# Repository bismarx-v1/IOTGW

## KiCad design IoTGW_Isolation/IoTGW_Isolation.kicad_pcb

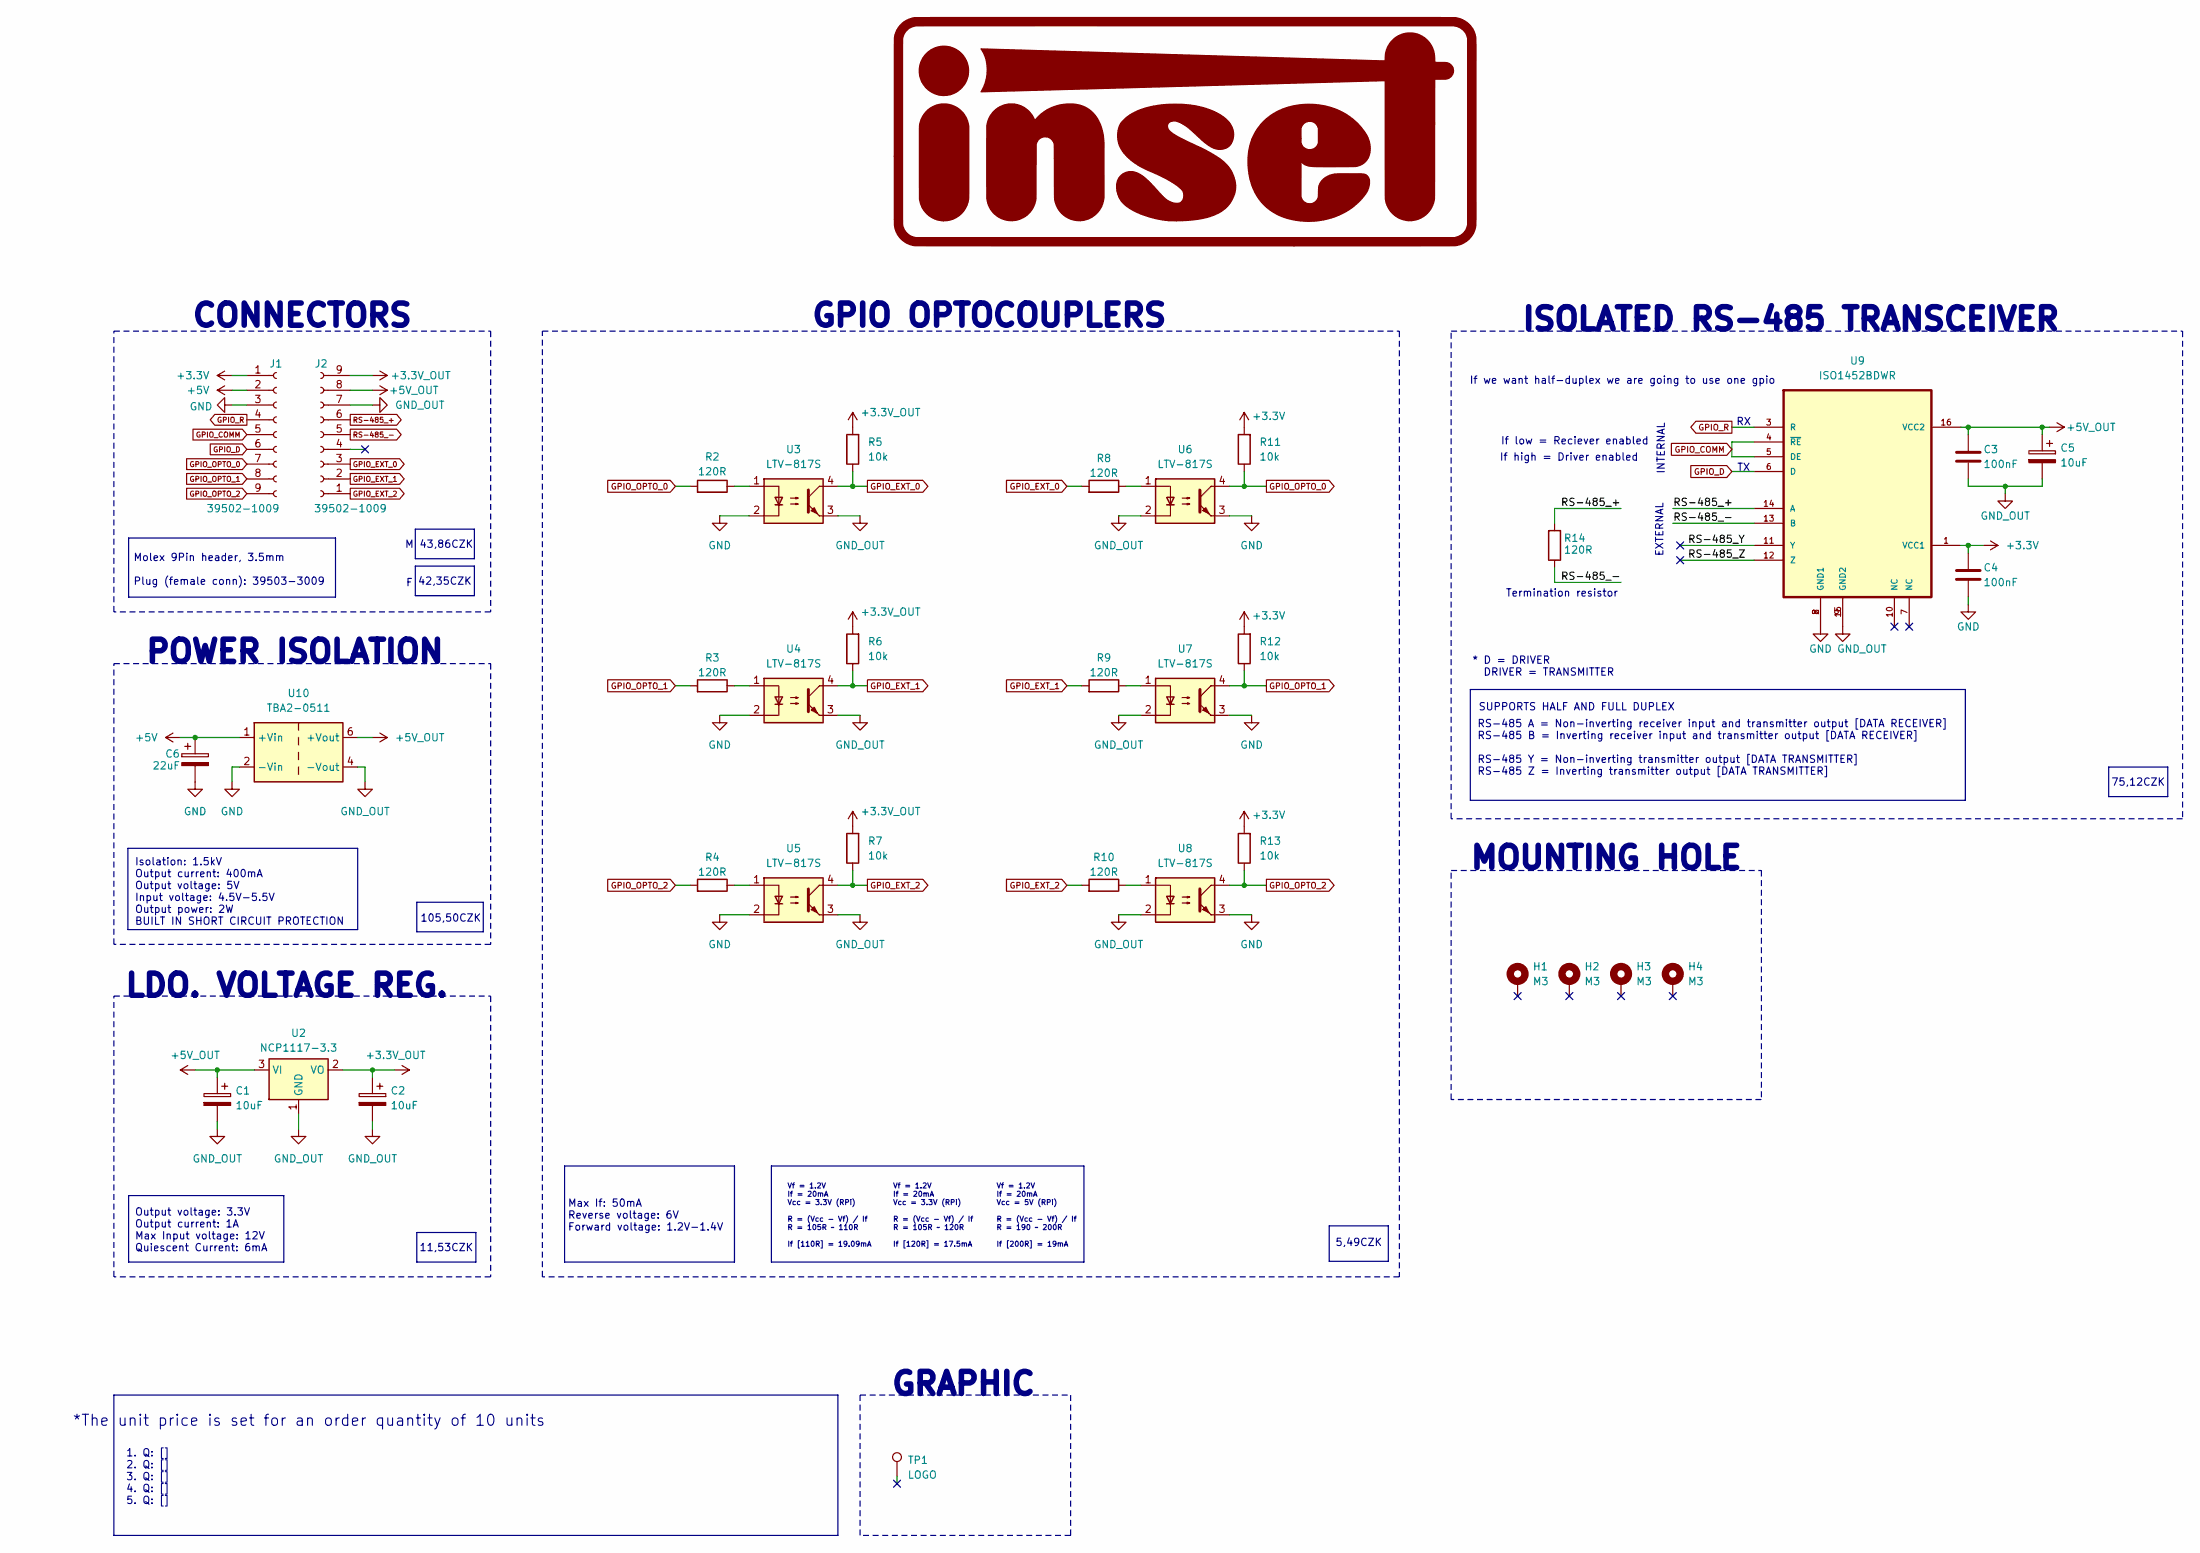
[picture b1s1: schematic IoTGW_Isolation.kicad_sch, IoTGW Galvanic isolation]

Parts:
C1, C2, C5: 10uF; CP_EIA-3216-18_Kemet-A_Pad1.58x1.35mm_HandSolder
C3, C4: 100nF; C_0805_2012Metric_Pad1.18x1.45mm_HandSolder
C6: 22uF; C_0805_2012Metric_Pad1.18x1.45mm_HandSolder
H1, H2, H3, H4: M3; MountingHole_3.2mm_M3_Pad_Via
J1, J2: 39502-1009; Molex_9pin_3.50
R2, R3, R4, R8, R9, R10, R14: 120R; R_0805_2012Metric_Pad1.20x1.40mm_HandSolder
R5, R6, R7, R11, R12, R13: 10k; R_0805_2012Metric_Pad1.20x1.40mm_HandSolder
TP1: LOGO; INSET_LOGO
U2: NCP1117-3.3; SOT-223-3_TabPin2
U3, U4, U5, U6, U7, U8: LTV-817S; SMDIP-4_W9.53mm
U9: ISO1452BDWR; SOIC-16W_7.5x10.3mm_P1.27mm
U10: TBA2-0511; Converter_DCDC_TRACO_TBA2-xxxx_Single_THT

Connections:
+3.3V: C4.1, J1.1, R11.2, R12.2, R13.2, U9.1 (VCC1)
+3.3V_OUT: C2.1, J2.9, R5.2, R6.2, R7.2, U2.2 (VO)
+5V: C6.1, J1.2, U10.1 (+Vin)
+5V_OUT: C1.1, C3.1, C5.1, J2.8, U2.3 (VI), U9.16 (VCC2), U10.6 (+Vout)
/RS-485_Y: U9.11 (Y)
/RS-485_Z: U9.12 (Z)
GND: C4.2, C6.2, J1.3, U3.2, U4.2, U5.2, U6.3, U7.3, U8.3, U9.2 (GND1), U9.8 (GND1), U10.2 (-Vin)
GND_OUT: C1.2, C2.2, C3.2, C5.2, J2.7, U2.1 (GND), U3.3, U4.3, U5.3, U6.2, U7.2, U8.2, U9.9 (GND2), U9.15 (GND2), U10.4 (-Vout)
GPIO_COMM: J1.5, U9.4 (~RE), U9.5 (DE)
GPIO_D: J1.6, U9.6 (D)
GPIO_EXT_0: J2.3, R5.1, R8.2, U3.4
GPIO_EXT_1: J2.2, R6.1, R9.2, U4.4
GPIO_EXT_2: J2.1, R7.1, R10.2, U5.4
GPIO_OPTO_0: J1.7, R2.2, R11.1, U6.4
GPIO_OPTO_1: J1.8, R3.2, R12.1, U7.4
GPIO_OPTO_2: J1.9, R4.2, R13.1, U8.4
GPIO_R: J1.4, U9.3 (R)
unnamed: R2.1, U3.1
unnamed: R3.1, U4.1
unnamed: R4.1, U5.1
unnamed: R8.1, U6.1
unnamed: R9.1, U7.1
unnamed: R10.1, U8.1
RS-485_+: J2.6, R14.2, U9.14 (A)
RS-485_-: J2.5, R14.1, U9.13 (B)

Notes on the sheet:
Vf = 1.2V If = 20mA Vcc = 5V (RPi) R = (Vcc - Vf) / If R = 190 ~ 200R If [200R] = 19mA
GRAPHIC
105,50CZK
42,35CZK
* D = DRIVER DRIVER = TRANSMITTER
If low = Reciever enabled
Molex 9Pin header, 3.5mm Plug (female conn): 39503-3009
Termination resistor
MOUNTING HOLE
If we want half-duplex we are going to use one gpio
ISOLATED RS-485 TRANSCEIVER
POWER ISOLATION
5,49CZK
GPIO OPTOCOUPLERS
1. Q: [] 2. Q: [] 3. Q: [] 4. Q: [] 5. Q: []
EXTERNAL
LDO. VOLTAGE REG.
Isolation: 1.5kV Output current: 400mA Output voltage: 5V Input voltage: 4.5V-5.5V Output power: 2W BUILT IN SHORT CIRCUIT PROTECTION
75,12CZK
INTERNAL
*The unit price is set for an order quantity of 10 units
CONNECTORS
Vf = 1.2V If = 20mA Vcc = 3.3V (RPi) R = (Vcc - Vf) / If R = 105R ~ 110R If [110R] = 19.09mA
11,53CZK
Output voltage: 3.3V Output current: 1A Max Input voltage: 12V Quiescent Current: 6mA
SUPPORTS HALF AND FULL DUPLEX
Max If: 50mA Reverse voltage: 6V Forward voltage: 1.2V-1.4V
RS-485 A = Non-inverting receiver input and transmitter output [DATA RECEIVER] RS-485 B = Inverting receiver input and transmitter output [DATA RECEIVER] RS-485 Y = Non-inverting transmitter output [DATA TRANSMITTER] RS-485 Z = Inverting transmitter output [DATA TRANSMITTER]
43,86CZK
Vf = 1.2V If = 20mA Vcc = 3.3V (RPi) R = (Vcc - Vf) / If R = 105R ~ 120R If [120R] = 17.5mA
If high = Driver enabled

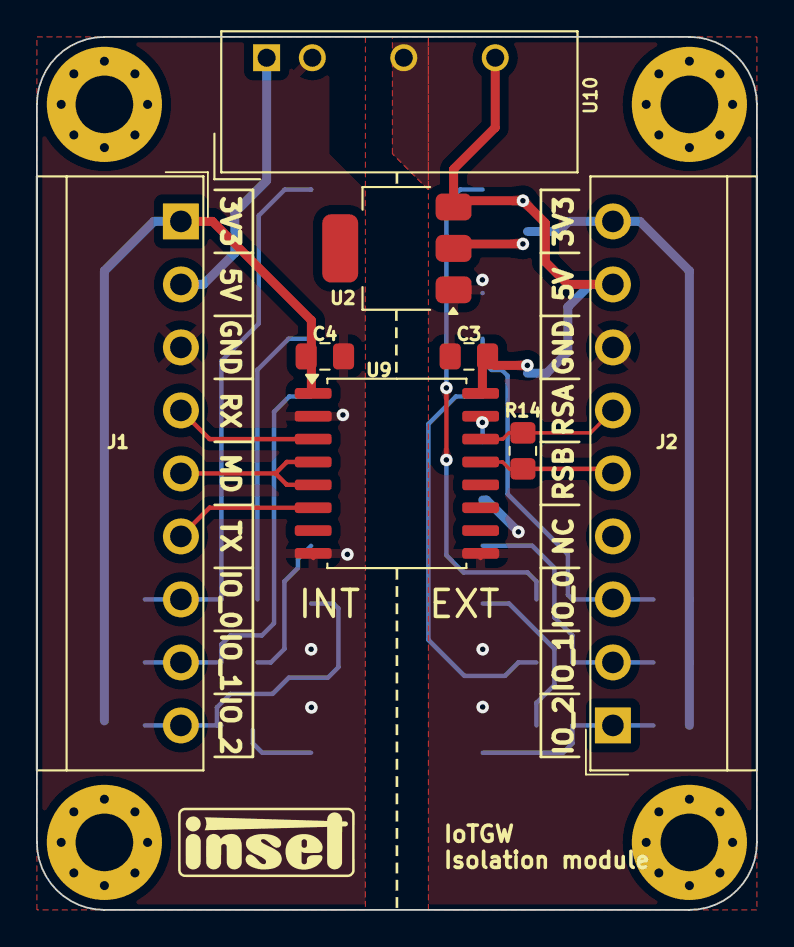
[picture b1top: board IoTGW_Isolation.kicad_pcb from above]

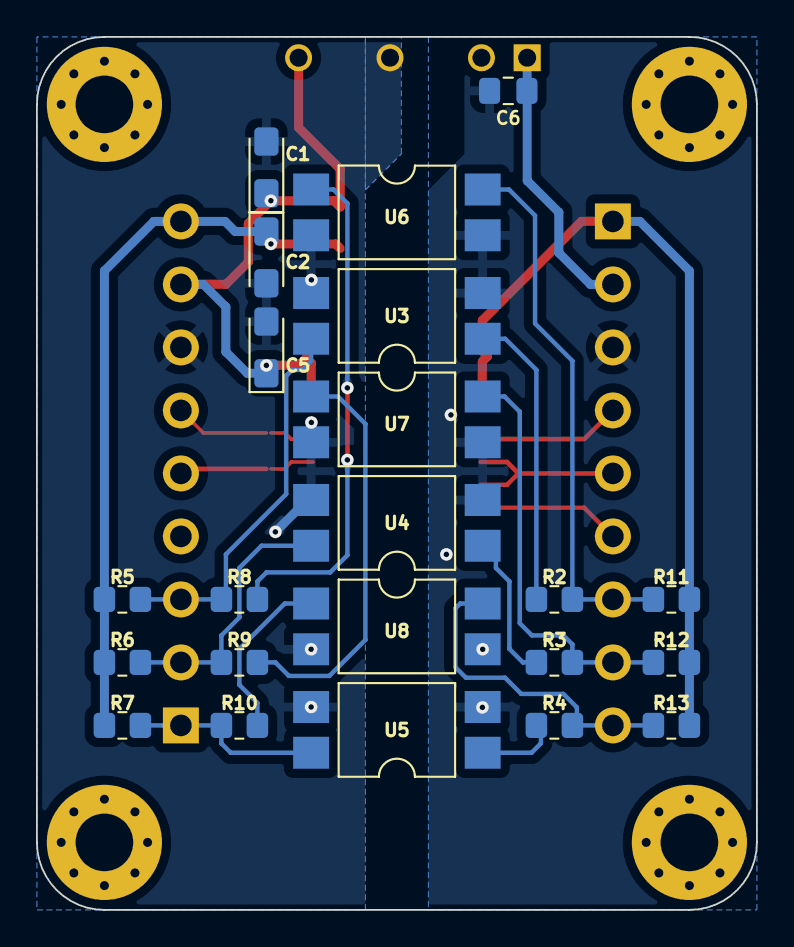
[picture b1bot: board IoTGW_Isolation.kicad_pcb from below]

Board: 2 copper layers, 40.0 x 48.5 mm, 35 parts (22 on the bottom side), 23 nets.

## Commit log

2025-01-11 alot of stuff
2025-01-11 gitignore
2025-01-12 reverse pol prot
2025-01-13 updated schematic - comp cost
2025-01-15 schematic upd
2025-01-16 Schematic update
2025-01-17 footprints + pcb
2025-01-18 PCB update, connectors 8pin
2025-01-20 PCB update
2025-01-23 PCB routing update
2025-01-23 pcb updates schemartic update
2025-01-23 step file
2025-01-23 pdfs
2025-01-24 smaller PCB
2025-01-27 to do list 3.3v logic update
2025-01-29 creatin of bom
2025-01-29 schematic update 3.3V logic
2025-01-30 3,3V logic update
2025-01-30 3v3 update
2025-01-30 bom update
2025-01-31 FInal PCB, plot, dimensions, 3D step file
2025-02-02 silskscreeen update
2025-02-03 last update, plot of IoTGW isolation
2025-02-03 PCB - ordered
